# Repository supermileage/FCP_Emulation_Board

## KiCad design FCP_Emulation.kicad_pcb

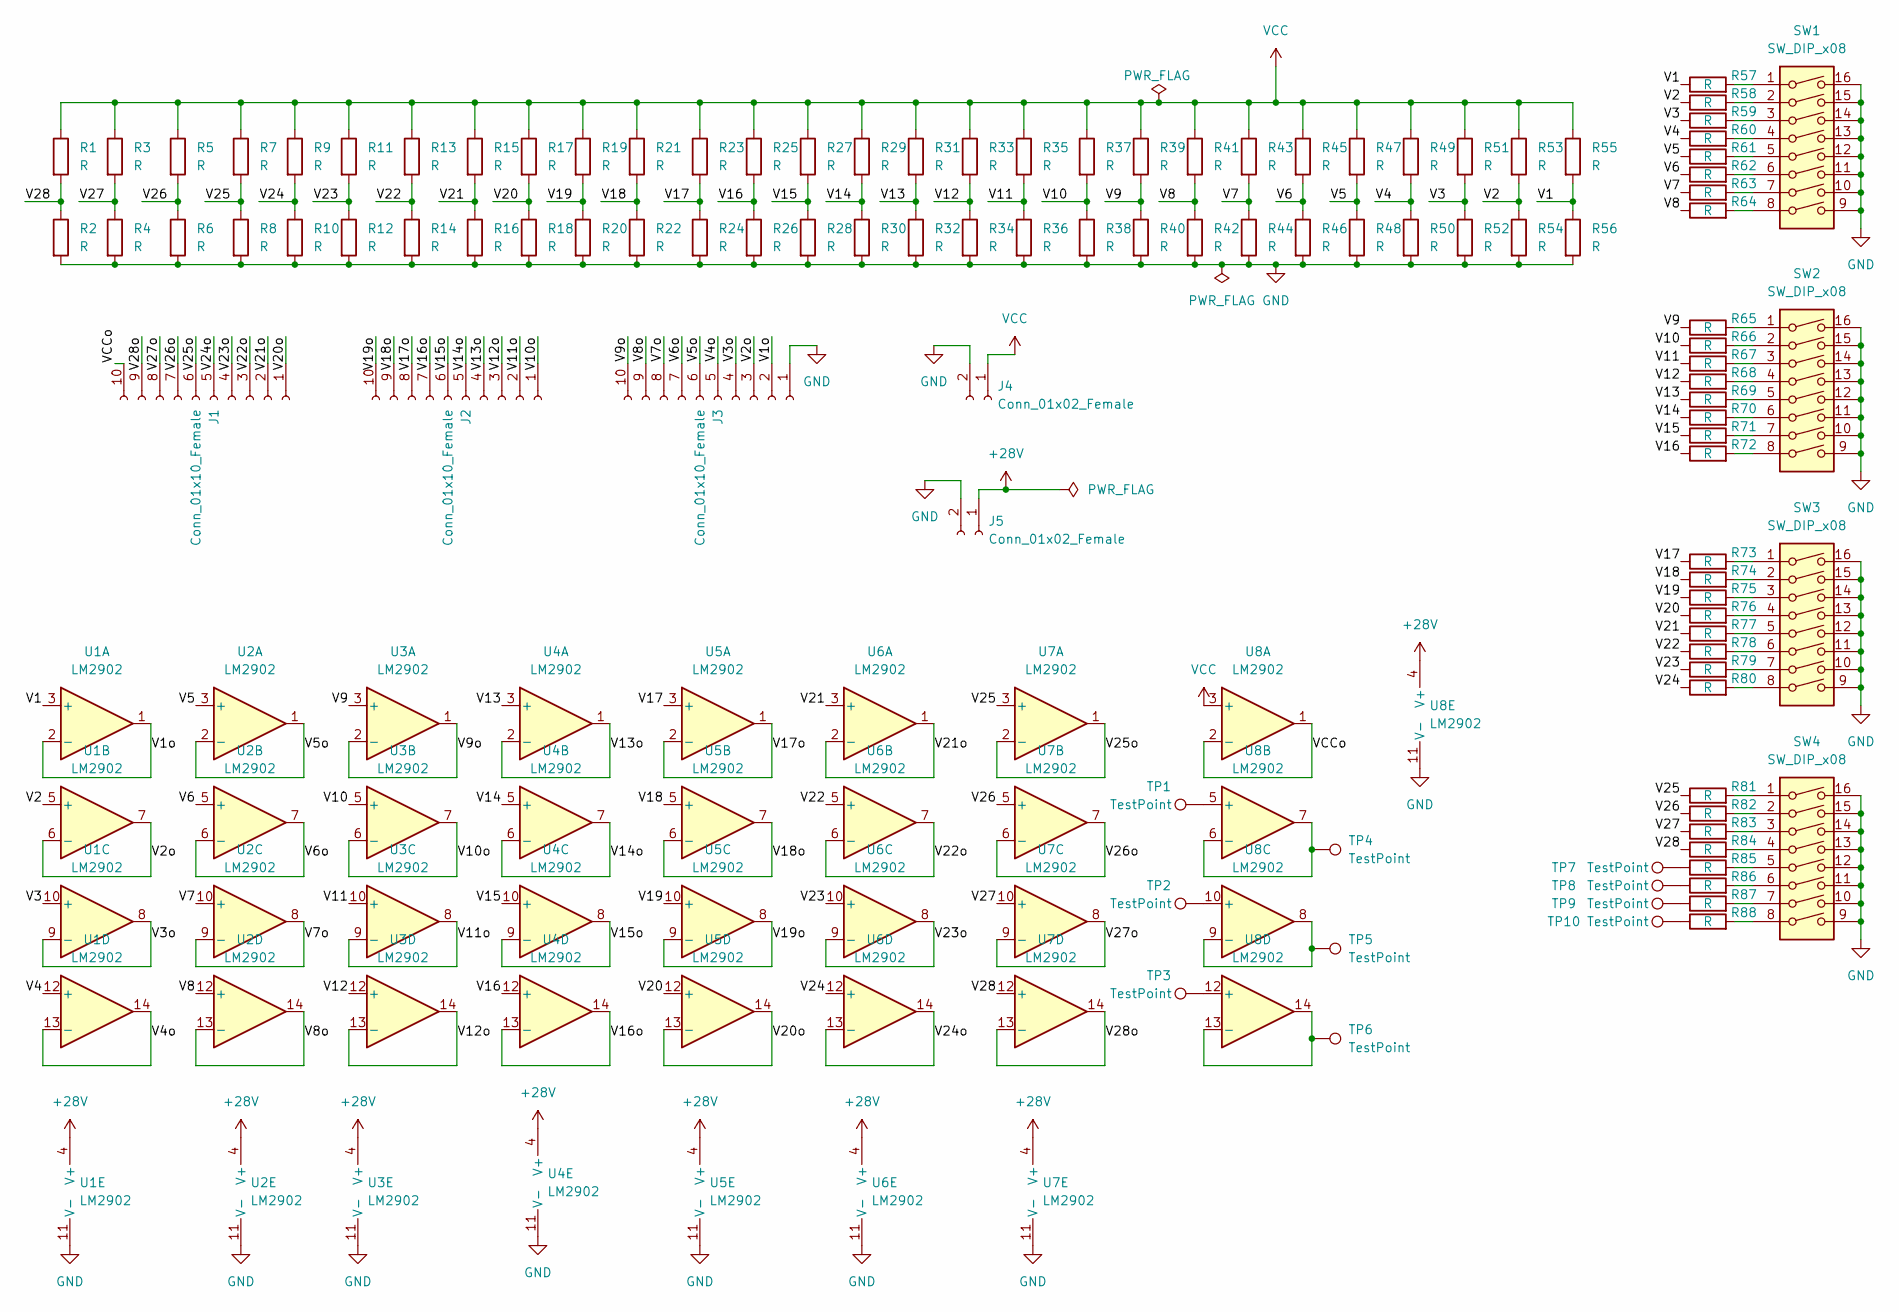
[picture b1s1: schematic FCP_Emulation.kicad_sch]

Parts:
J1, J2, J3: Conn_01x10_Female; PhoenixContact_MCV_1,5_10-G-3.5_1x10_P3.50mm_Vertical
J4, J5: Conn_01x02_Female; Molex_Mini-Fit_Jr_5569-02A2_2x01_P4.20mm_Horizontal
R1, R2, R3, R4, R5, R6, R7, R8, R9, R10, R11, R12, R13, R14, R15, R16, R17, R18, R19, R20, R21, R22, R23, R24, R25, R26, R27, R28, R29, R30, R31, R32, R33, R34, R35, R36, R37, R38, R39, R40, R41, R42, R43, R44, R45, R46, R47, R48, R49, R50, R51, R52, R53, R54, R55, R56, R57, R58, R59, R60, R61, R62, R63, R64, R65, R66, R67, R68, R69, R70, R71, R72, R73, R74, R75, R76, R77, R78, R79, R80, R81, R82, R83, R84, R85, R86, R87, R88: R; R_0805_2012Metric
SW1, SW2, SW3, SW4: SW_DIP_x08; DIP-16_W7.62mm
TP1, TP2, TP3, TP4, TP5, TP6, TP7, TP8, TP9, TP10: TestPoint; PinHeader_1x01_P2.54mm_Vertical
U1, U2, U3, U4, U5, U6, U7, U8: LM2902; SO-14_3.9x8.65mm_P1.27mm

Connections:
+28V: J5.1, U1.4 (V+), U2.4 (V+), U3.4 (V+), U4.4 (V+), U5.4 (V+), U6.4 (V+), U7.4 (V+), U8.4 (V+)
/V1: R55.2, R56.1, R57.1, U1.3 (+)
/V1o: J3.2, U1.1, U1.2 (-)
/V2: R53.2, R54.1, R58.1, U1.5 (+)
/V2o: J3.3, U1.6 (-), U1.7
/V3: R51.2, R52.1, R59.1, U1.10 (+)
/V3o: J3.4, U1.8, U1.9 (-)
/V4: R49.2, R50.1, R60.1, U1.12 (+)
/V4o: J3.5, U1.13 (-), U1.14
/V5: R47.2, R48.1, R61.1, U2.3 (+)
/V5o: J3.6, U2.1, U2.2 (-)
/V6: R45.2, R46.1, R62.1, U2.5 (+)
/V6o: J3.7, U2.6 (-), U2.7
/V7: R43.2, R44.1, R63.1, U2.10 (+)
/V7o: J3.8, U2.8, U2.9 (-)
/V8: R41.2, R42.1, R64.1, U2.12 (+)
/V8o: J3.9, U2.13 (-), U2.14
/V9: R39.2, R40.1, R65.1, U3.3 (+)
/V9o: J3.10, U3.1, U3.2 (-)
/V10: R37.2, R38.1, R66.1, U3.5 (+)
/V10o: J2.1, U3.6 (-), U3.7
/V11: R35.2, R36.1, R67.1, U3.10 (+)
/V11o: J2.2, U3.8, U3.9 (-)
/V12: R33.2, R34.1, R68.1, U3.12 (+)
/V12o: J2.3, U3.13 (-), U3.14
/V13: R31.2, R32.1, R69.1, U4.3 (+)
/V13o: J2.4, U4.1, U4.2 (-)
/V14: R29.2, R30.1, R70.1, U4.5 (+)
/V14o: J2.5, U4.6 (-), U4.7
/V15: R27.2, R28.1, R71.1, U4.10 (+)
/V15o: J2.6, U4.8, U4.9 (-)
/V16: R25.2, R26.1, R72.1, U4.12 (+)
/V16o: J2.7, U4.13 (-), U4.14
/V17: R23.2, R24.1, R73.1, U5.3 (+)
/V17o: J2.8, U5.1, U5.2 (-)
/V18: R21.2, R22.1, R74.1, U5.5 (+)
/V18o: J2.9, U5.6 (-), U5.7
/V19: R19.2, R20.1, R75.1, U5.10 (+)
/V19o: J2.10, U5.8, U5.9 (-)
/V20: R17.2, R18.1, R76.1, U5.12 (+)
/V20o: J1.1, U5.13 (-), U5.14
/V21: R15.2, R16.1, R77.1, U6.3 (+)
/V21o: J1.2, U6.1, U6.2 (-)
/V22: R13.2, R14.1, R78.1, U6.5 (+)
/V22o: J1.3, U6.6 (-), U6.7
/V23: R11.2, R12.1, R79.1, U6.10 (+)
/V23o: J1.4, U6.8, U6.9 (-)
/V24: R9.2, R10.1, R80.1, U6.12 (+)
/V24o: J1.5, U6.13 (-), U6.14
/V25: R7.2, R8.1, R81.1, U7.3 (+)
/V25o: J1.6, U7.1, U7.2 (-)
/V26: R5.2, R6.1, R82.1, U7.5 (+)
/V26o: J1.7, U7.6 (-), U7.7
/V27: R3.2, R4.1, R83.1, U7.10 (+)
/V27o: J1.8, U7.8, U7.9 (-)
/V28: R1.2, R2.1, R84.1, U7.12 (+)
/V28o: J1.9, U7.13 (-), U7.14
/VCCo: J1.10, U8.1, U8.2 (-)
GND: J3.1, J4.2, J5.2, R2.2, R4.2, R6.2, R8.2, R10.2, R12.2, R14.2, R16.2, R18.2, R20.2, R22.2, R24.2, R26.2, R28.2, R30.2, R32.2, R34.2, R36.2, R38.2, R40.2, R42.2, R44.2, R46.2, R48.2, R50.2, R52.2, R54.2, R56.2, SW1.9, SW1.10, SW1.11, SW1.12, SW1.13, SW1.14, SW1.15, SW1.16, SW2.9, SW2.10, SW2.11, SW2.12, SW2.13, SW2.14, SW2.15, SW2.16, SW3.9, SW3.10, SW3.11, SW3.12, SW3.13, SW3.14, SW3.15, SW3.16, SW4.9, SW4.10, SW4.11, SW4.12, SW4.13, SW4.14, SW4.15, SW4.16, U1.11 (V-), U2.11 (V-), U3.11 (V-), U4.11 (V-), U5.11 (V-), U6.11 (V-), U7.11 (V-), U8.11 (V-)
unnamed: R57.2, SW1.1
unnamed: R58.2, SW1.2
unnamed: R59.2, SW1.3
unnamed: R60.2, SW1.4
unnamed: R61.2, SW1.5
unnamed: R62.2, SW1.6
unnamed: R63.2, SW1.7
unnamed: R64.2, SW1.8
unnamed: R65.2, SW2.1
unnamed: R66.2, SW2.2
unnamed: R67.2, SW2.3
unnamed: R68.2, SW2.4
unnamed: R69.2, SW2.5
unnamed: R70.2, SW2.6
unnamed: R71.2, SW2.7
unnamed: R72.2, SW2.8
unnamed: R73.2, SW3.1
unnamed: R74.2, SW3.2
unnamed: R75.2, SW3.3
unnamed: R76.2, SW3.4
unnamed: R77.2, SW3.5
unnamed: R78.2, SW3.6
unnamed: R79.2, SW3.7
unnamed: R80.2, SW3.8
unnamed: R81.2, SW4.1
unnamed: R82.2, SW4.2
unnamed: R83.2, SW4.3
unnamed: R84.2, SW4.4
unnamed: R85.1, TP7.1
unnamed: R85.2, SW4.5
unnamed: R86.1, TP8.1
unnamed: R86.2, SW4.6
unnamed: R87.1, TP9.1
unnamed: R87.2, SW4.7
unnamed: R88.1, TP10.1
unnamed: R88.2, SW4.8
unnamed: TP1.1, U8.5 (+)
unnamed: TP2.1, U8.10 (+)
unnamed: TP3.1, U8.12 (+)
unnamed: TP4.1, U8.6 (-), U8.7
unnamed: TP5.1, U8.8, U8.9 (-)
unnamed: TP6.1, U8.13 (-), U8.14
VCC: J4.1, R1.1, R3.1, R5.1, R7.1, R9.1, R11.1, R13.1, R15.1, R17.1, R19.1, R21.1, R23.1, R25.1, R27.1, R29.1, R31.1, R33.1, R35.1, R37.1, R39.1, R41.1, R43.1, R45.1, R47.1, R49.1, R51.1, R53.1, R55.1, U8.3 (+)

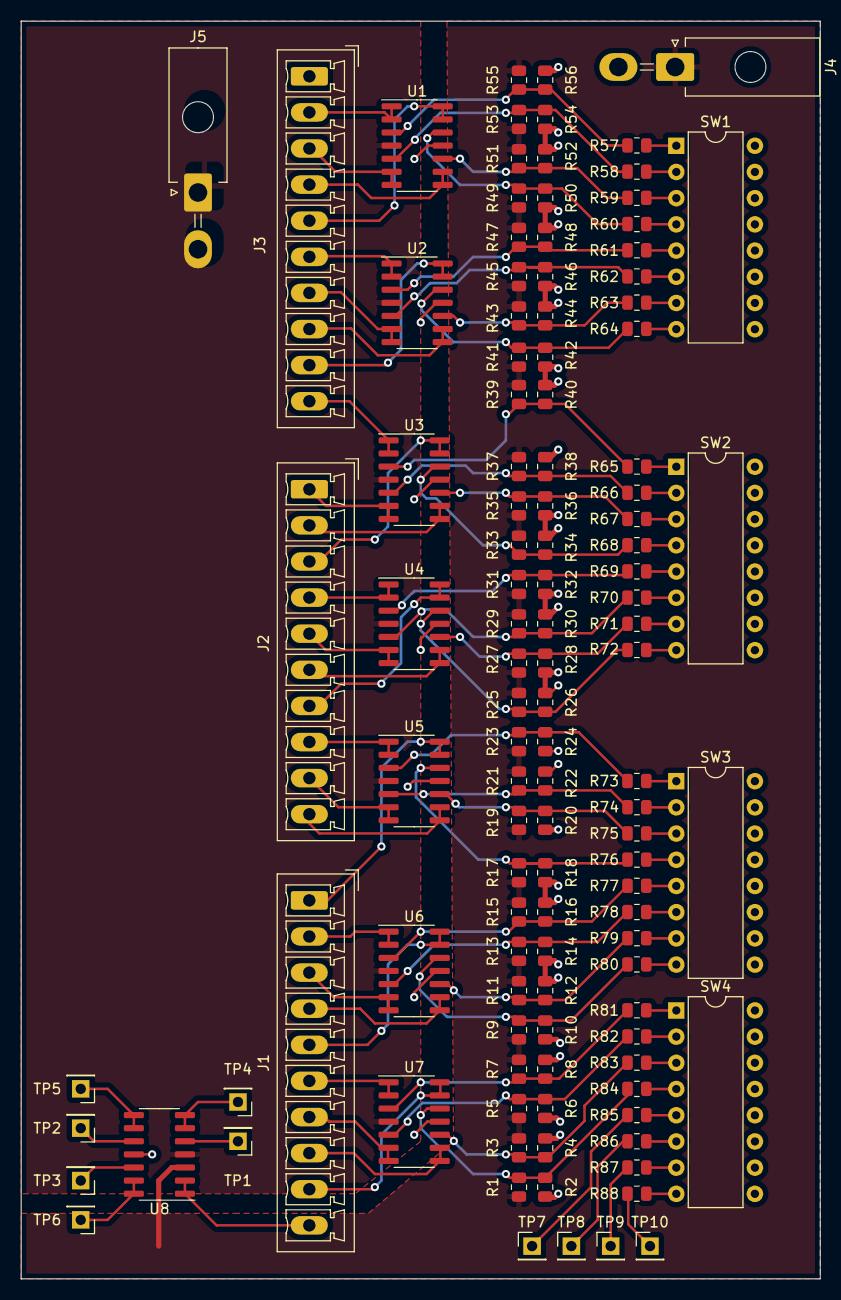
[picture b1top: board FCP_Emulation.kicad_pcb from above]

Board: 2 copper layers, 77.5 x 121.9 mm, 115 parts (0 on the bottom side), 102 nets.

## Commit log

2023-11-04 deleted a bunch of old stuff, added microcontroller, new op amp circuits
2023-11-07 created the op amp cases
2023-11-11 changed op amp circuit values based on breadboarding and simualtion
2024-01-20 added negative case schematic
2024-01-20 added voltage divider on negative case
2024-01-20 added lt1111 symbol
2024-01-20 Specced out negative case circuit
2024-01-24 positive case specced
2024-01-27 fixed some ERC errors
2024-01-27 updated flags and 5V regulator
2024-02-03 re-added buffers and added positive case for the negative case circuit
2024-02-10 Added datasheets and footprints to most components
2024-02-10 added inductor footprints and resistor values
2024-02-17 resistor grid specced but still have to double check connections
2024-02-17 ok ive updated the connections but someone shld really look this over
2024-09-23 added op amp power connector and changed op amp power source. pwm case needs to be checked
